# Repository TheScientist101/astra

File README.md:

<h1 align="center">astra</h1>

<h3 align="center">An open source, low cost, extensible brushed drone.</h3>

## What is Astra?

Astra is an `~80mm` brushed quadcopter. It it powered off of a single 1s Li-Po (`4.2V`), and uses four brushed motors.

Astra supports an optional FPV module, and includes a HAT-style pin interface on the flight controller.

We've also designed our own transmitter for Astra. The flight controller and transmitter use an `nRF24` to communicate with low latency.

Every part of Astra was designed from scratch - the flight controller, the transmitter, and the frame.

## Why is Astra?

Siddhant and I both love making things, but we've never made anything that moves before. What cooler of a thing is there that moves than a drone? With air voyage in our control, it would open the gate to even cooler projects, like imagine if you could play laser tag with a drone as your teammate or if you could have a drone that follows you around and takes pictures of you. The possibilities are endless!

That's why we decided to make our drone extensible. To me, modularity is the coolest part of any gadget. It allows you to add new features and capabilities without having to redesign the entire thing. Astra has a HAT-style pin interface called the DUCKDUCKGOOSE (Digital Unified Centralized Kibibit Device Universal Coding Knowledge Generic Operable Objective Service Extensible) Connector on the flight controller, which allows you to add new peripherals and sensors easily.

On the other hand, most drone projects we've seen online are expensive. While Hack Club is dope enough to have a [program that gives us free hardware](https://highway.hackclub.com), it is difficult to find a "DIY" drone that is relatively cheap that flies well. Since we wanted to make sure that our drone was actually good at flying, we decided to remove the onboard camera that we had in our initial design in place of a more traditional FPV system rather than just trying to make our own.

## Cost

All of the components for the drone and can be bought for around `$75`. (See the [`BOM`](./BOM.md) for more details!)

The bulk of this is actually the cost to buy the PCBs and stencil (which is anticipated to be around `$25`). The actual component cost is closer to `$50`.

> Note:
> Adding an FPV system to the drone is relatively costly. The FPV Camera + VTX module costs `$25`, which is actually on the cheaper end for these systems. The total cost with the FPV module is slightly less than `$100` before taxes and other fees.

(for hackclub) Even though the total cost of this drone is under `$150`, we will likely need to have multiple iterations of the PCB before we can get it working right.

## Technical Details

The Flight Controller uses an `STM32H750`. This is a powerful chip with plenty of GPIO pins for peripherals. We plan to implement a software OSD within the H7 for the FPV interface.

PCB files can be found within the `drone/pcb/` folder.

The Flight Controller uses the [betaflight](https://betaflight.com/) firmware. A betaflight config file as well as flashing instructions can be found in the `drone/firmware/` folder

The frame for the FC was designed in Onshape. CAD files can be found in `drone/cad/`;

**Peripherals**:

- `BMI270` - IMU
- `BMP388` - Barometer
- 2 `WS2812B`s
- 2 configurable buttons
- microSD Card Socket
- A 22 pin header for HAT-style extensions. Includes SWD, UART, SPI, I2C, and extra GPIOs.
- An extra UART connector.

The Ground Transmitter uses an `ESP32-C3-SuperMini` (a C3 chip similar to the XIAO that we already have on hand). It features:

- 3 `WS2812B`s
- 2 Joysticks, configured for mode 2 control
- 4 configurable buttons (+2 from the joysticks)

The PCB, firmware, and case for the transmitter can be found in the `controller/` folder

## Pictures

[**Full Schematic PDF**](assets/schematic.pdf)

**Copper Layers:**

**PCB 3D Render:**

**Controller PCB Render:**

**Controller Assembled Render:**

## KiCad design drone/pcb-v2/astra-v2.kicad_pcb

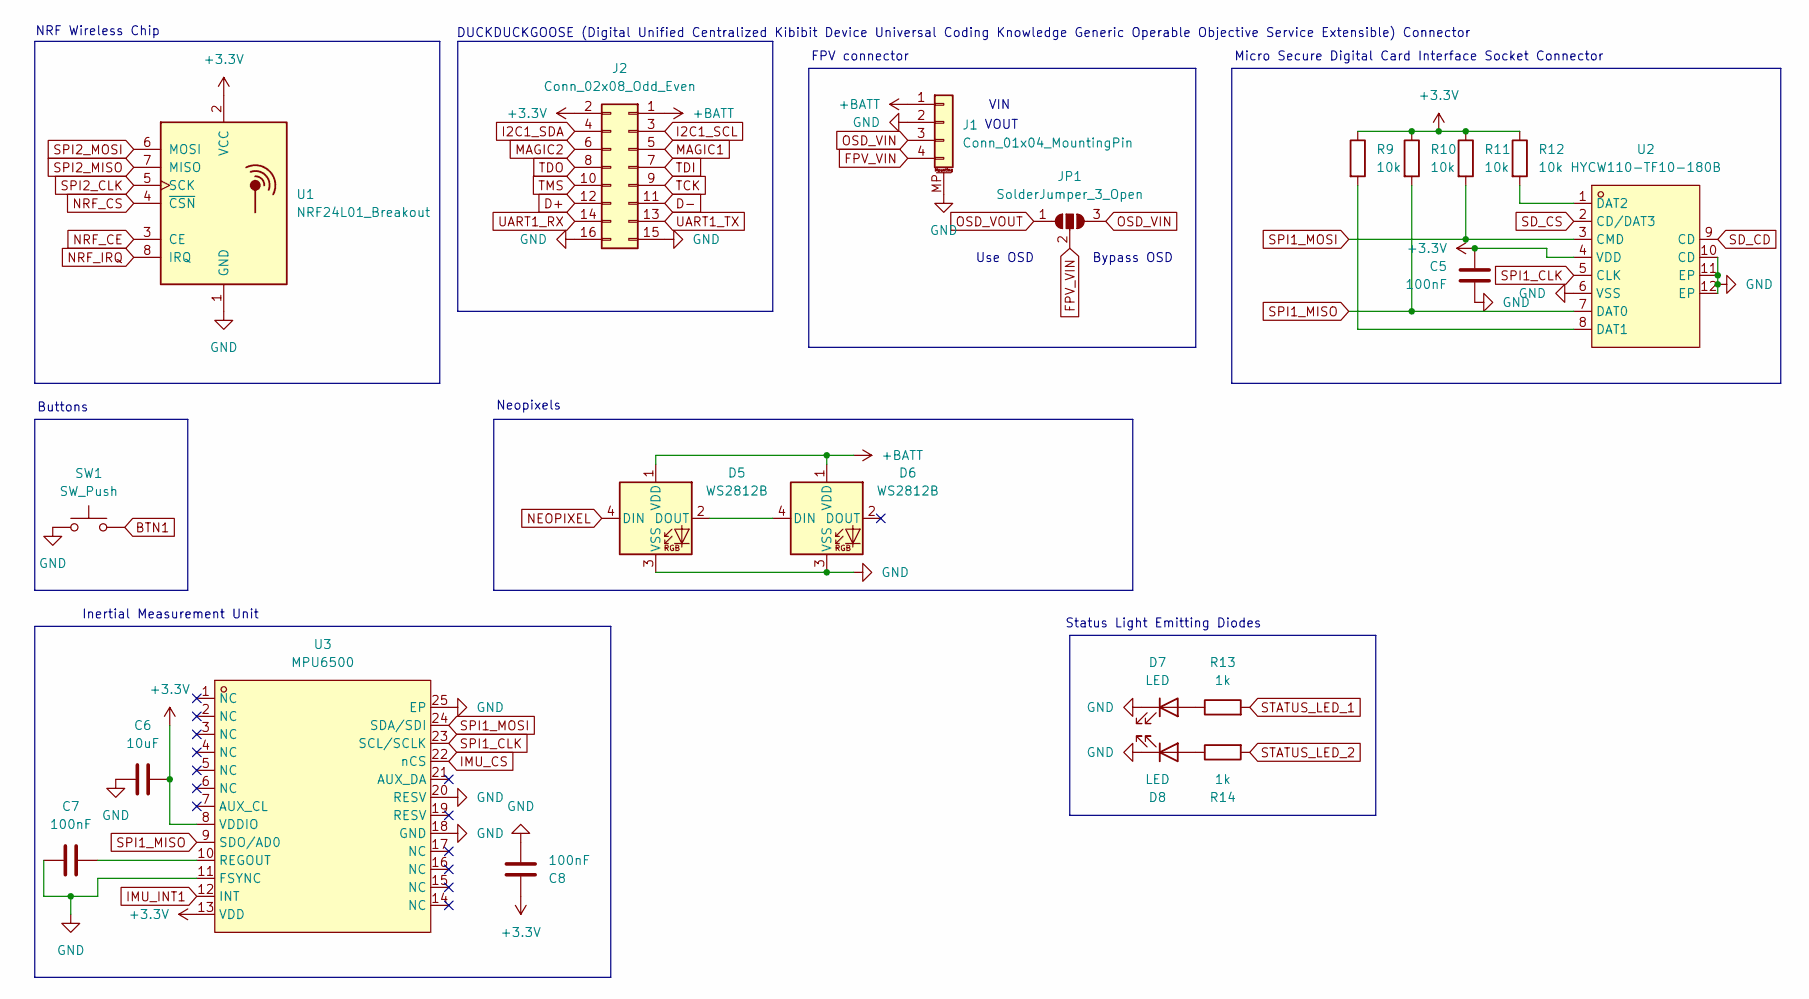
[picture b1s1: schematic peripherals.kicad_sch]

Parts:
C5: 100nF; C_0805_2012Metric_Pad1.18x1.45mm_HandSolder
C6: 10uF; C_0603_1608Metric
C7, C8: 100nF; C_0603_1608Metric; LCSC C14663
D5, D6: WS2812B; LED_WS2812B_PLCC4_5.0x5.0mm_P3.2mm
D7, D8: LED; LED_0805_2012Metric
J1: Conn_01x04_MountingPin; JST_SH_BM04B-SRSS-TB_1x04-1MP_P1.00mm_Vertical
J2: Conn_02x08_Odd_Even; PinHeader_2x08_P2.54mm_Vertical
JP1: SolderJumper_3_Open; SolderJumper-3_P1.3mm_Open_RoundedPad1.0x1.5mm
R9, R10, R11, R12: 10k; R_0805_2012Metric; LCSC C17414
R13, R14: 1k; R_0805_2012Metric_Pad1.20x1.40mm_HandSolder
SW1: SW_Push; SW-SMD_L4.0-W2.9-LS5.0
U1: NRF24L01_Breakout; nRF24L01_SMD_Breakout
U2: HYCW110-TF10-180B; SIM-SMD_HYCW110-TF10-180B; LCSC Part C2962030
U3: MPU6500; QFN-24-1EP_3x3mm_P0.4mm_EP1.75x1.6mm; LCSC C50278

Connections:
+3.3V: C5.1, C6.2, C8.1, J2.2, R9.1, R10.1, R11.1, R12.1, U1.2 (VCC), U2.4 (VDD), U3.8 (VDDIO), U3.13 (VDD); also elsewhere on the board
+BATT: D5.1 (VDD), D6.1 (VDD), J1.1, J2.1; also elsewhere on the board
BTN1: SW1.2; also elsewhere on the board
D+: J2.12; also elsewhere on the board
D-: J2.11; also elsewhere on the board
FPV_VIN: J1.4, JP1.2 (C)
GND: C5.2, C6.1, C7.2, C8.2, D5.3 (VSS), D6.3 (VSS), D7.1 (K), D8.1 (K), J1.2, J1.MP (MountPin), J2.15, J2.16, SW1.1, U1.1 (GND), U2.6 (VSS), U2.10 (CD), U2.11 (EP), U2.12 (EP), U3.11 (FSYNC), U3.18 (GND), U3.20 (RESV), U3.25 (EP); also elsewhere on the board
I2C1_SCL: J2.3; also elsewhere on the board
I2C1_SDA: J2.4; also elsewhere on the board
IMU_CS: U3.22 (nCS); also elsewhere on the board
IMU_INT1: U3.12 (INT); also elsewhere on the board
MAGIC1: J2.5; also elsewhere on the board
MAGIC2: J2.6; also elsewhere on the board
NEOPIXEL: D5.4 (DIN); also elsewhere on the board
NRF_CE: U1.3 (CE); also elsewhere on the board
NRF_CS: U1.4 (~CSN); also elsewhere on the board
NRF_IRQ: U1.8 (IRQ); also elsewhere on the board
unnamed: D5.2 (DOUT), D6.4 (DIN)
unnamed: D7.2 (A), R13.1
unnamed: D8.2 (A), R14.1
unnamed: R9.2, U2.8 (DAT1)
unnamed: R12.2, U2.1 (DAT2)
unnamed: C7.1, U3.10 (REGOUT)
OSD_VIN: J1.3, JP1.3 (B)
OSD_VOUT: JP1.1 (A)
SD_CD: U2.9 (CD); also elsewhere on the board
SD_CS: U2.2 (CD/DAT3); also elsewhere on the board
SPI1_CLK: U2.5 (CLK), U3.23 (SCL/SCLK); also elsewhere on the board
SPI1_MISO: R10.2, U2.7 (DAT0), U3.9 (SDO/AD0); also elsewhere on the board
SPI1_MOSI: R11.2, U2.3 (CMD), U3.24 (SDA/SDI); also elsewhere on the board
SPI2_CLK: U1.5 (SCK); also elsewhere on the board
SPI2_MISO: U1.7 (MISO); also elsewhere on the board
SPI2_MOSI: U1.6 (MOSI); also elsewhere on the board
STATUS_LED_1: R13.2; also elsewhere on the board
STATUS_LED_2: R14.2; also elsewhere on the board
TCK: J2.9; also elsewhere on the board
TDI: J2.7; also elsewhere on the board
TDO: J2.8; also elsewhere on the board
TMS: J2.10; also elsewhere on the board
UART1_RX: J2.14; also elsewhere on the board
UART1_TX: J2.13; also elsewhere on the board

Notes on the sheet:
Buttons
FPV connector
Neopixels
DUCKDUCKGOOSE (Digital Unified Centralized Kibibit Device Universal Coding Knowledge Generic Operable Objective Service Extensible) Connector
Use OSD
NRF Wireless Chip
Status Light Emitting Diodes
VOUT
Bypass OSD
Micro Secure Digital Card Interface Socket Connector
Inertial Measurement Unit
VIN

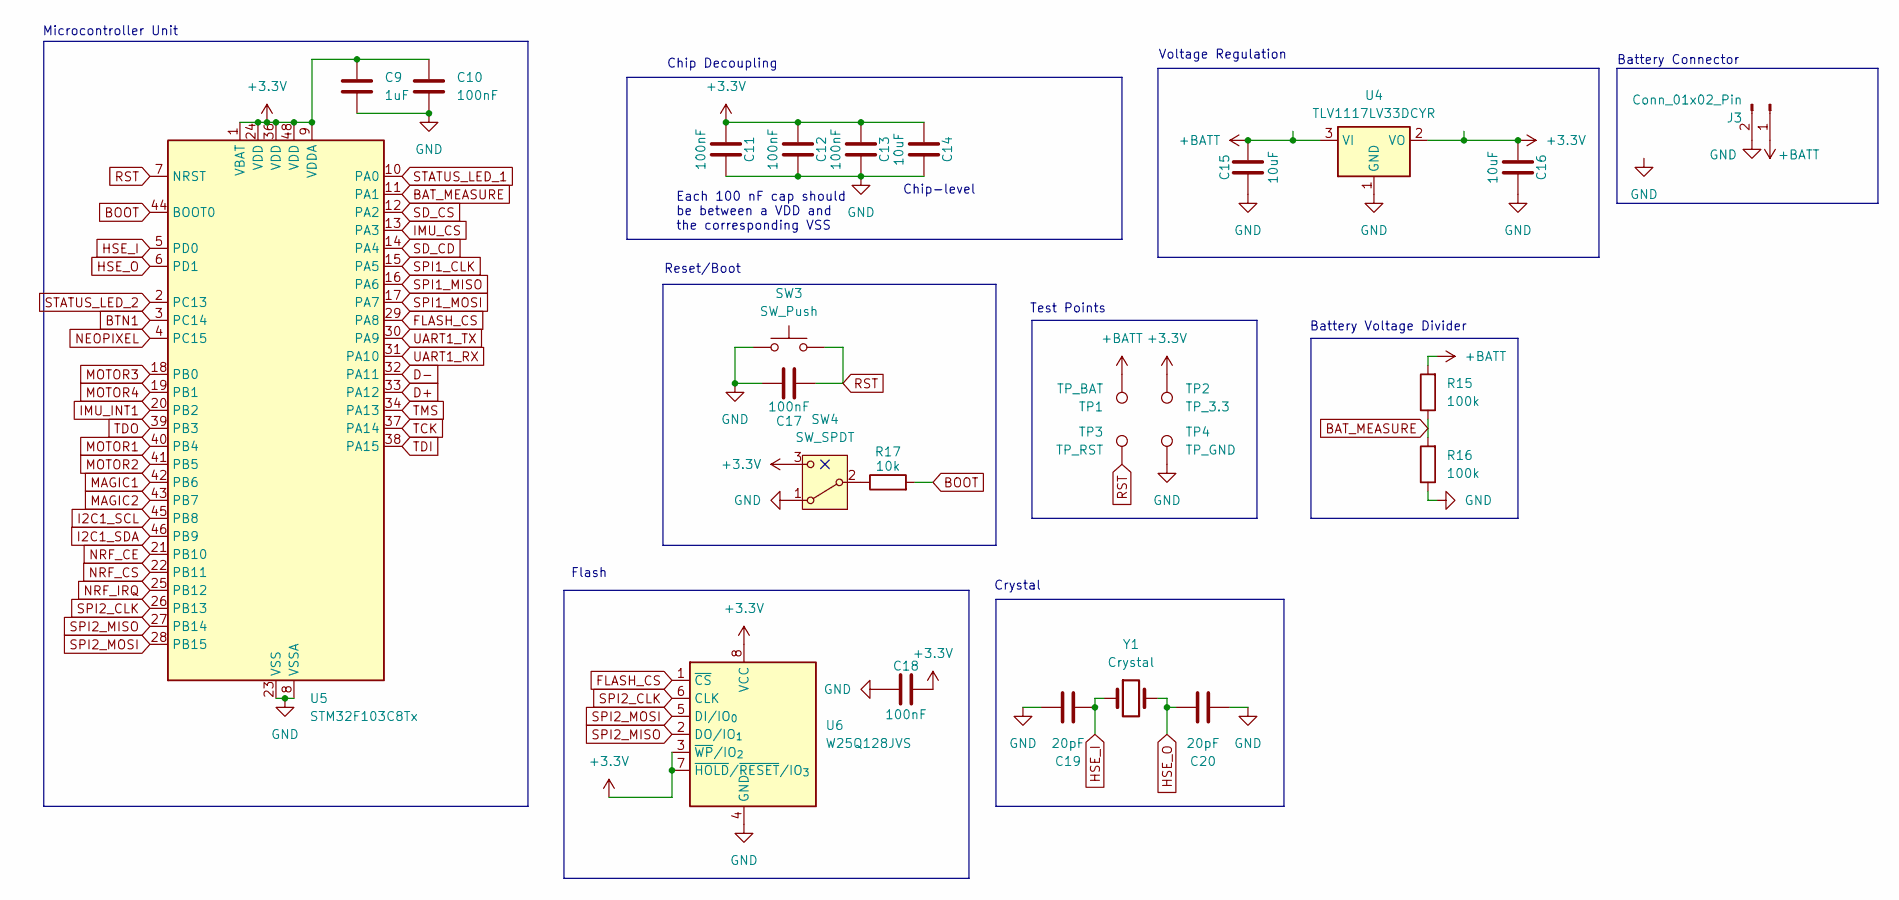
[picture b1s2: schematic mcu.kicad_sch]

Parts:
C9: 1uF; C_0603_1608Metric; LCSC C15849
C10, C11, C12, C13, C18: 100nF; C_0603_1608Metric; LCSC C14663
C14: 10uF; C_0603_1608Metric; LCSC C19702
C15, C16: 10uF; C_0805_2012Metric_Pad1.18x1.45mm_HandSolder
C17: 100nF; C_0805_2012Metric_Pad1.18x1.45mm_HandSolder
C19, C20: 20pF; C_0603_1608Metric; LCSC C1648
J3: Conn_01x02_Pin; SolderWire-0.1sqmm_1x02_P3.6mm_D0.4mm_OD1mm
R15, R16: 100k; R_0603_1608Metric; LCSC C25803
R17: 10k; R_0805_2012Metric; LCSC C17414
SW3: SW_Push; SW-SMD_L4.0-W2.9-LS5.0
SW4: SW_SPDT; SW_Slide-03_Wuerth-WS-SLTV_10x2.5x6.4_P2.54mm
TP1: TP_BAT; TestPoint_Pad_D2.0mm
TP2: TP_3.3; TestPoint_Pad_D2.0mm
TP3: TP_RST; TestPoint_Pad_D2.0mm
TP4: TP_GND; TestPoint_Pad_D2.0mm
U4: TLV1117LV33DCYR; SOT-223-3_TabPin2
U5: STM32F103C8Tx; LQFP-48_7x7mm_P0.5mm; LCSC C8734
U6: W25Q128JVS; SOIC-8_5.3x5.3mm_P1.27mm; LCSC C97521
Y1: Crystal; Crystal_SMD_5032-2Pin_5.0x3.2mm; LCSC C115962

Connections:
+3.3V: C9.1, C10.1, C11.1, C12.1, C13.1, C14.1, C16.1, C18.2, SW4.3 (C), TP2.1, U4.2 (VO), U5.1 (VBAT), U5.9 (VDDA), U5.24 (VDD), U5.36 (VDD), U5.48 (VDD), U6.3 (~WP/IO_{2}), U6.7 (~HOLD/~RESET/IO_{3}), U6.8 (VCC); also elsewhere on the board
+BATT: C15.2, J3.1, R15.2, TP1.1, U4.3 (VI); also elsewhere on the board
BAT_MEASURE: R15.1, R16.2, U5.11 (PA1)
BOOT: R17.2, U5.44 (BOOT0)
BTN1: U5.3 (PC14); also elsewhere on the board
D+: U5.33 (PA12); also elsewhere on the board
D-: U5.32 (PA11); also elsewhere on the board
FLASH_CS: U5.29 (PA8), U6.1 (~CS)
GND: C9.2, C10.2, C11.2, C12.2, C13.2, C14.2, C15.1, C16.2, C17.2, C18.1, C19.1, C20.2, J3.2, R16.1, SW3.1, SW4.1 (A), TP4.1, U4.1 (GND), U5.8 (VSSA), U5.23 (VSS), U5.35 (VSS), U5.47 (VSS), U6.4 (GND); also elsewhere on the board
HSE_I: C19.2, U5.5 (PD0), Y1.1
HSE_O: C20.1, U5.6 (PD1), Y1.2
I2C1_SCL: U5.45 (PB8); also elsewhere on the board
I2C1_SDA: U5.46 (PB9); also elsewhere on the board
IMU_CS: U5.13 (PA3); also elsewhere on the board
IMU_INT1: U5.20 (PB2); also elsewhere on the board
MAGIC1: U5.42 (PB6); also elsewhere on the board
MAGIC2: U5.43 (PB7); also elsewhere on the board
MOTOR1: U5.40 (PB4); also elsewhere on the board
MOTOR2: U5.41 (PB5); also elsewhere on the board
MOTOR3: U5.18 (PB0); also elsewhere on the board
MOTOR4: U5.19 (PB1); also elsewhere on the board
NEOPIXEL: U5.4 (PC15); also elsewhere on the board
NRF_CE: U5.21 (PB10); also elsewhere on the board
NRF_CS: U5.22 (PB11); also elsewhere on the board
NRF_IRQ: U5.25 (PB12); also elsewhere on the board
unnamed: R17.1, SW4.2 (B)
RST: C17.1, SW3.2, TP3.1, U5.7 (NRST)
SD_CD: U5.14 (PA4); also elsewhere on the board
SD_CS: U5.12 (PA2); also elsewhere on the board
SPI1_CLK: U5.15 (PA5); also elsewhere on the board
SPI1_MISO: U5.16 (PA6); also elsewhere on the board
SPI1_MOSI: U5.17 (PA7); also elsewhere on the board
SPI2_CLK: U5.26 (PB13), U6.6 (CLK); also elsewhere on the board
SPI2_MISO: U5.27 (PB14), U6.2 (DO/IO_{1}); also elsewhere on the board
SPI2_MOSI: U5.28 (PB15), U6.5 (DI/IO_{0}); also elsewhere on the board
STATUS_LED_1: U5.10 (PA0); also elsewhere on the board
STATUS_LED_2: U5.2 (PC13); also elsewhere on the board
TCK: U5.37 (PA14); also elsewhere on the board
TDI: U5.38 (PA15); also elsewhere on the board
TDO: U5.39 (PB3); also elsewhere on the board
TMS: U5.34 (PA13); also elsewhere on the board
UART1_RX: U5.31 (PA10); also elsewhere on the board
UART1_TX: U5.30 (PA9); also elsewhere on the board

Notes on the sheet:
Microcontroller Unit
Flash
Each 100 nF cap should be between a VDD and the corresponding VSS
Battery Voltage Divider
Chip Decoupling
Crystal
Test Points
Chip-level
Battery Connector
Reset/Boot
Voltage Regulation

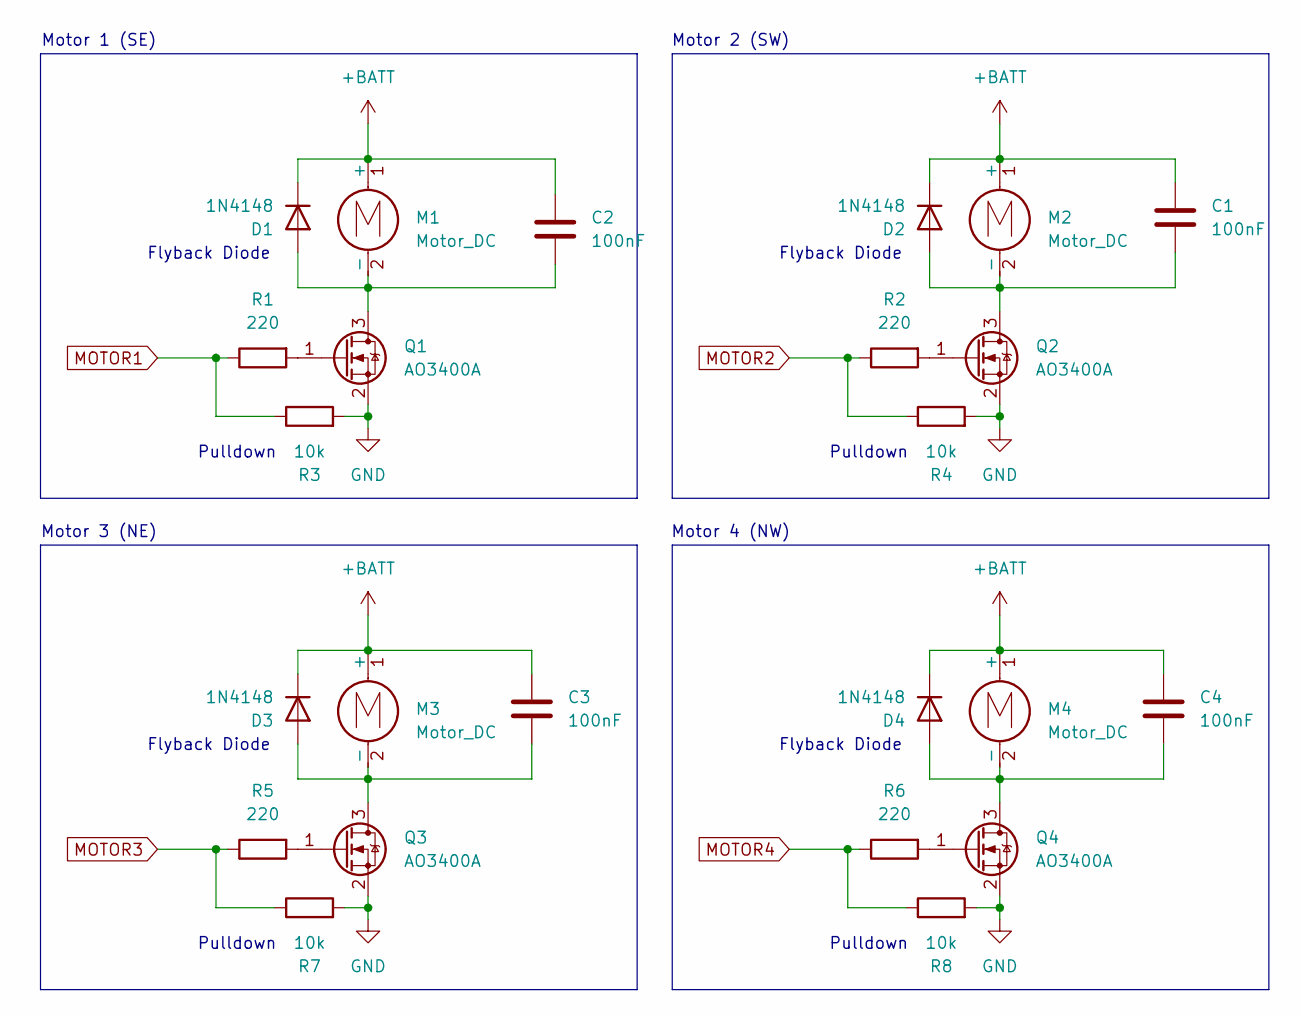
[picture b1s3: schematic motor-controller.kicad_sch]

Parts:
C1, C2, C3, C4: 100nF; C_0805_2012Metric_Pad1.18x1.45mm_HandSolder
D1, D2, D3, D4: 1N4148; D_SOD-323; LCSC C2128
M1, M2, M3, M4: Motor_DC; SolderWire-0.1sqmm_1x02_P3.6mm_D0.4mm_OD1mm
Q1, Q2, Q3, Q4: AO3400A; SOT-23-3; LCSC C20917
R1, R2, R5, R6: 220; R_0805_2012Metric; LCSC C17557
R3, R4, R7, R8: 10k; R_0805_2012Metric; LCSC C17414

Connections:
+BATT: C1.1, C2.1, C3.1, C4.1, D1.1 (K), D2.1 (K), D3.1 (K), D4.1 (K), M1.1 (+), M2.1 (+), M3.1 (+), M4.1 (+); also elsewhere on the board
GND: Q1.2 (S), Q2.2 (S), Q3.2 (S), Q4.2 (S), R3.2, R4.2, R7.2, R8.2; also elsewhere on the board
MOTOR1: R1.1, R3.1; also elsewhere on the board
MOTOR2: R2.1, R4.1; also elsewhere on the board
MOTOR3: R5.1, R7.1; also elsewhere on the board
MOTOR4: R6.1, R8.1; also elsewhere on the board
unnamed: C2.2, D1.2 (A), M1.2 (-), Q1.3 (D)
unnamed: C1.2, D2.2 (A), M2.2 (-), Q2.3 (D)
unnamed: C3.2, D3.2 (A), M3.2 (-), Q3.3 (D)
unnamed: C4.2, D4.2 (A), M4.2 (-), Q4.3 (D)
unnamed: Q1.1 (G), R1.2
unnamed: Q2.1 (G), R2.2
unnamed: Q3.1 (G), R5.2
unnamed: Q4.1 (G), R6.2

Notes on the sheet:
Pulldown
Motor 2 (SW)
Flyback Diode
Motor 1 (SE)
Motor 3 (NE)
Motor 4 (NW)

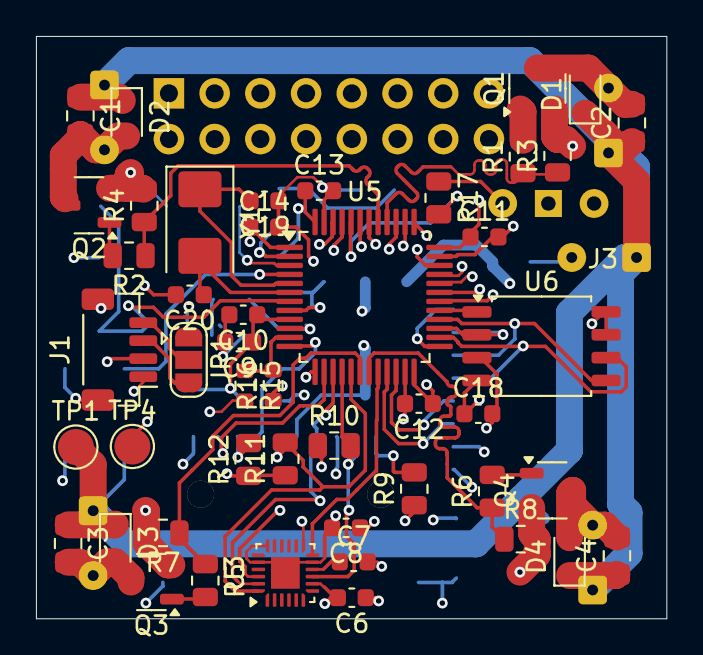
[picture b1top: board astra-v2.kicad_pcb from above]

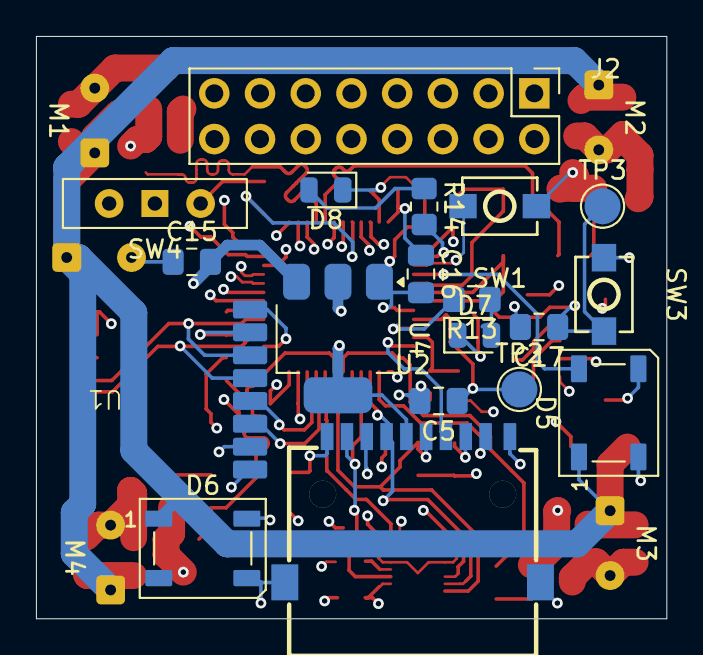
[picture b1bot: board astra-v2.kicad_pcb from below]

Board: 4 copper layers, 35.0 x 32.3 mm, 71 parts (23 on the bottom side), 59 nets.

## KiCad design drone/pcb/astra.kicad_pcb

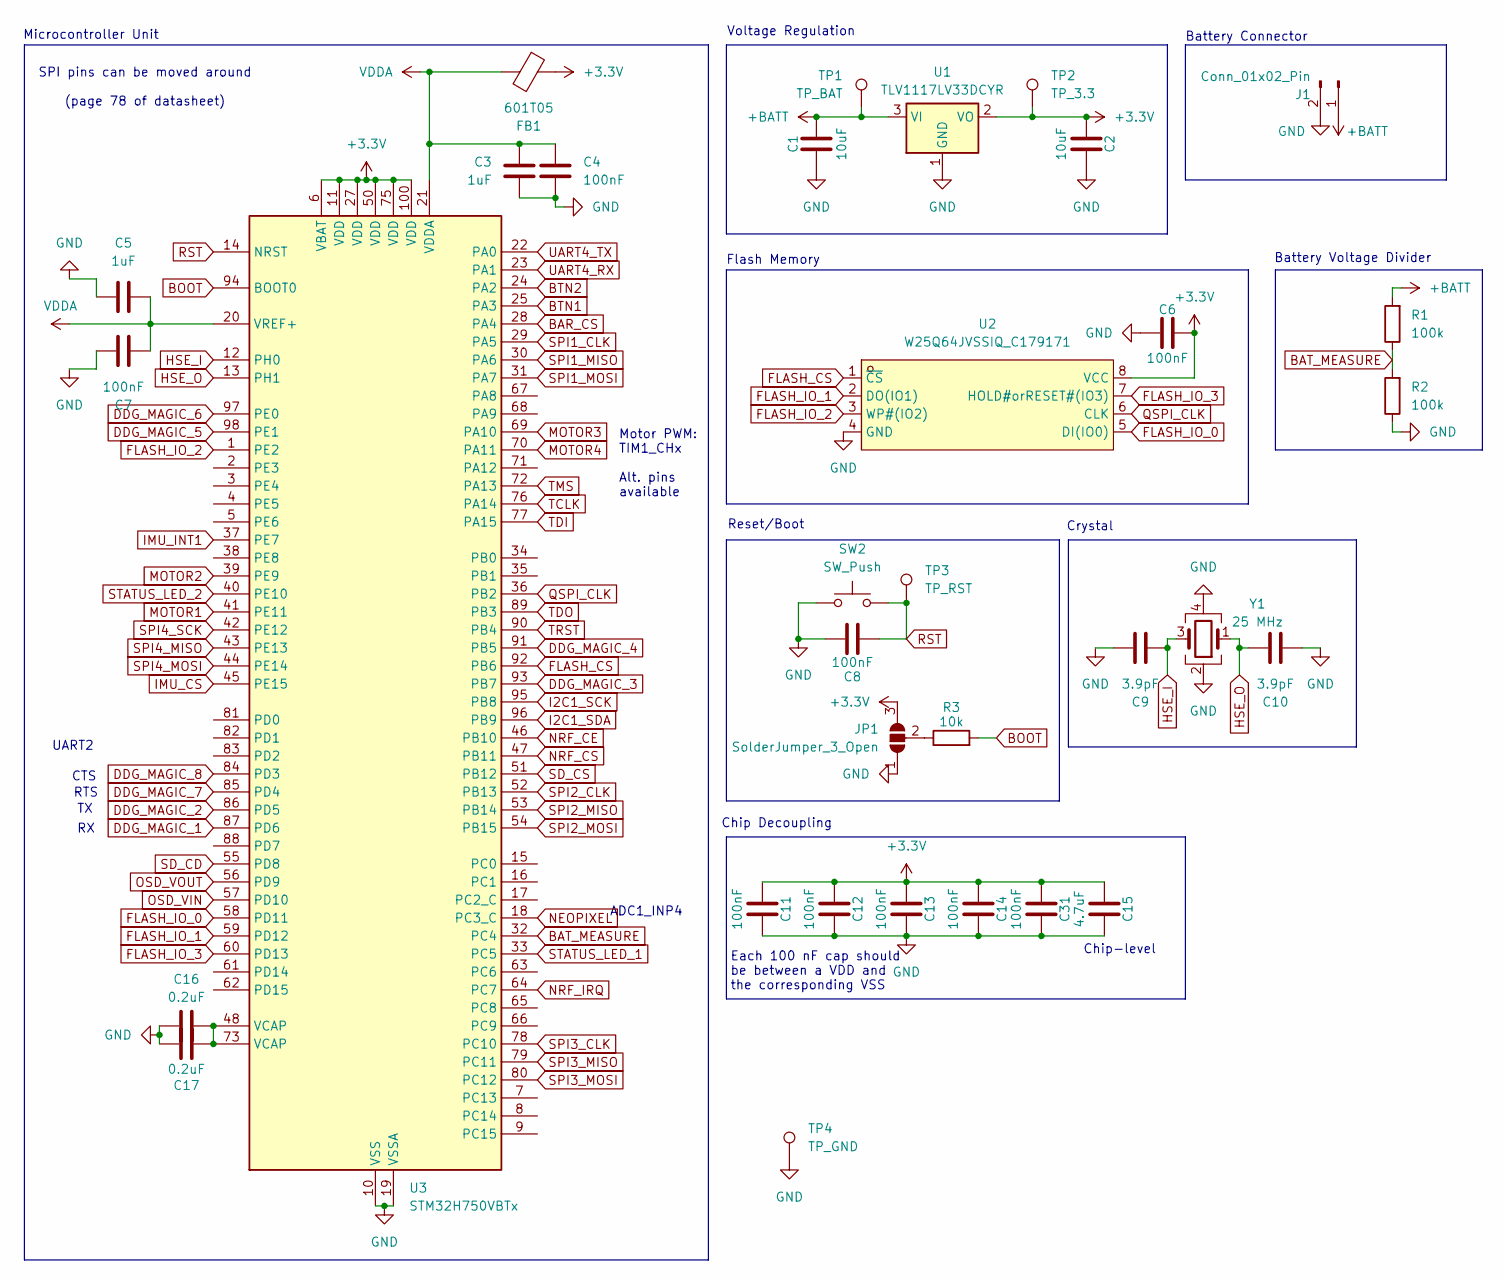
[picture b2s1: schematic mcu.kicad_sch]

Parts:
C1, C2: 10uF; C_0805_2012Metric_Pad1.18x1.45mm_HandSolder
C3, C5: 1uF; C_0805_2012Metric_Pad1.18x1.45mm_HandSolder
C4, C6, C7, C8, C11, C12, C13, C14, C31: 100nF; C_0805_2012Metric_Pad1.18x1.45mm_HandSolder
C9, C10: 3.9pF; C_0603_1608Metric_Pad1.08x0.95mm_HandSolder
C15: 4.7uF; C_0805_2012Metric_Pad1.18x1.45mm_HandSolder
C16, C17: 0.2uF; C_0805_2012Metric_Pad1.18x1.45mm_HandSolder
FB1: 601T05; L_0603_1608Metric_Pad1.05x0.95mm_HandSolder
J1: Conn_01x02_Pin; SolderWire-0.1sqmm_1x02_P3.6mm_D0.4mm_OD1mm
JP1: SolderJumper_3_Open; SolderJumper-3_P1.3mm_Open_RoundedPad1.0x1.5mm
R1, R2: 100k; R_0805_2012Metric_Pad1.20x1.40mm_HandSolder
R3: 10k; R_0805_2012Metric_Pad1.20x1.40mm_HandSolder
SW2: SW_Push; SW-SMD_L4.0-W2.9-LS5.0
TP1: TP_BAT; TestPoint_Pad_D2.0mm
TP2: TP_3.3; TestPoint_Pad_D2.0mm
TP3: TP_RST; TestPoint_Pad_D2.0mm
TP4: TP_GND; TestPoint_Pad_D2.0mm
U1: TLV1117LV33DCYR; SOT-223-3_TabPin2
U2: W25Q64JVSSIQ_C179171; SOIC-8_5.3x5.3mm_P1.27mm; LCSC Part C179171
U3: STM32H750VBTx; LQFP-100_14x14mm_P0.5mm
Y1: 25 MHz; Crystal_SMD_3225-4Pin_3.2x2.5mm_HandSoldering

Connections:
+3.3V: C2.1, C6.2, C11.1, C12.1, C13.1, C14.1, C15.1, C31.1, FB1.1, JP1.3 (B), TP2.1, U1.2 (VO), U2.8 (VCC), U3.6 (VBAT), U3.11 (VDD), U3.27 (VDD), U3.50 (VDD), U3.75 (VDD), U3.100 (VDD); also elsewhere on the board
+BATT: C1.2, J1.1, R1.2, TP1.1, U1.3 (VI); also elsewhere on the board
BAR_CS: U3.28 (PA4); also elsewhere on the board
BAT_MEASURE: R1.1, R2.2, U3.32 (PC4)
BOOT: R3.2, U3.94 (BOOT0)
BTN1: U3.25 (PA3); also elsewhere on the board
BTN2: U3.24 (PA2); also elsewhere on the board
DDG_MAGIC_1: U3.87 (PD6); also elsewhere on the board
DDG_MAGIC_2: U3.86 (PD5); also elsewhere on the board
DDG_MAGIC_3: U3.93 (PB7); also elsewhere on the board
DDG_MAGIC_4: U3.91 (PB5); also elsewhere on the board
DDG_MAGIC_5: U3.98 (PE1); also elsewhere on the board
DDG_MAGIC_6: U3.97 (PE0); also elsewhere on the board
DDG_MAGIC_7: U3.85 (PD4); also elsewhere on the board
DDG_MAGIC_8: U3.84 (PD3); also elsewhere on the board
FLASH_CS: U2.1 (~CS), U3.92 (PB6)
FLASH_IO_0: U2.5 (DI(IO0)), U3.58 (PD11)
FLASH_IO_1: U2.2 (DO(IO1)), U3.59 (PD12)
FLASH_IO_2: U2.3 (WP#(IO2)), U3.1 (PE2)
FLASH_IO_3: U2.7 (HOLD#orRESET#(IO3)), U3.60 (PD13)
GND: C1.1, C2.2, C3.2, C4.2, C5.1, C6.1, C7.1, C8.2, C9.1, C10.2, C11.2, C12.2, C13.2, C14.2, C15.2, C16.1, C17.1, C31.2, J1.2, JP1.1 (A), R2.1, SW2.1, TP4.1, U1.1 (GND), U2.4 (GND), U3.10 (VSS), U3.19 (VSSA), U3.26 (VSS), U3.49 (VSS), U3.74 (VSS), U3.99 (VSS), Y1.2, Y1.4; also elsewhere on the board
HSE_I: C9.2, U3.12 (PH0), Y1.3
HSE_O: C10.1, U3.13 (PH1), Y1.1
I2C1_SCK: U3.95 (PB8); also elsewhere on the board
I2C1_SDA: U3.96 (PB9); also elsewhere on the board
IMU_CS: U3.45 (PE15); also elsewhere on the board
IMU_INT1: U3.37 (PE7); also elsewhere on the board
MOTOR1: U3.41 (PE11); also elsewhere on the board
MOTOR2: U3.39 (PE9); also elsewhere on the board
MOTOR3: U3.69 (PA10); also elsewhere on the board
MOTOR4: U3.70 (PA11); also elsewhere on the board
NEOPIXEL: U3.18 (PC3_C); also elsewhere on the board
NRF_CE: U3.46 (PB10); also elsewhere on the board
NRF_CS: U3.47 (PB11); also elsewhere on the board
NRF_IRQ: U3.64 (PC7); also elsewhere on the board
unnamed: C16.2, C17.2, U3.48 (VCAP), U3.73 (VCAP)
unnamed: JP1.2 (C), R3.1
OSD_VIN: U3.57 (PD10); also elsewhere on the board
OSD_VOUT: U3.56 (PD9); also elsewhere on the board
QSPI_CLK: U2.6 (CLK), U3.36 (PB2)
RST: C8.1, SW2.2, TP3.1, U3.14 (NRST); also elsewhere on the board
SD_CD: U3.55 (PD8); also elsewhere on the board
SD_CS: U3.51 (PB12); also elsewhere on the board
SPI1_CLK: U3.29 (PA5); also elsewhere on the board
SPI1_MISO: U3.30 (PA6); also elsewhere on the board
SPI1_MOSI: U3.31 (PA7); also elsewhere on the board
SPI2_CLK: U3.52 (PB13); also elsewhere on the board
SPI2_MISO: U3.53 (PB14); also elsewhere on the board
SPI2_MOSI: U3.54 (PB15); also elsewhere on the board
SPI3_CLK: U3.78 (PC10); also elsewhere on the board
SPI3_MISO: U3.79 (PC11); also elsewhere on the board
SPI3_MOSI: U3.80 (PC12); also elsewhere on the board
SPI4_MISO: U3.43 (PE13); also elsewhere on the board
SPI4_MOSI: U3.44 (PE14); also elsewhere on the board
SPI4_SCK: U3.42 (PE12); also elsewhere on the board
STATUS_LED_1: U3.33 (PC5); also elsewhere on the board
STATUS_LED_2: U3.40 (PE10); also elsewhere on the board
TCLK: U3.76 (PA14); also elsewhere on the board
TDI: U3.77 (PA15); also elsewhere on the board
TDO: U3.89 (PB3); also elsewhere on the board
TMS: U3.72 (PA13); also elsewhere on the board
TRST: U3.90 (PB4); also elsewhere on the board
UART4_RX: U3.23 (PA1); also elsewhere on the board
UART4_TX: U3.22 (PA0); also elsewhere on the board
VDDA: C3.1, C4.1, C5.2, C7.2, FB1.2, U3.20 (VREF+), U3.21 (VDDA)

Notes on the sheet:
Reset/Boot
Crystal
Voltage Regulation
UART2
CTS
Chip-level
Battery Connector
Flash Memory
Battery Voltage Divider
Microcontroller Unit
Each 100 nF cap should be between a VDD and the corresponding VSS
SPI pins can be moved around (page 78 of datasheet)
ADC1_INP4
Motor PWM: TIM1_CHx Alt. pins available
RTS
Chip Decoupling

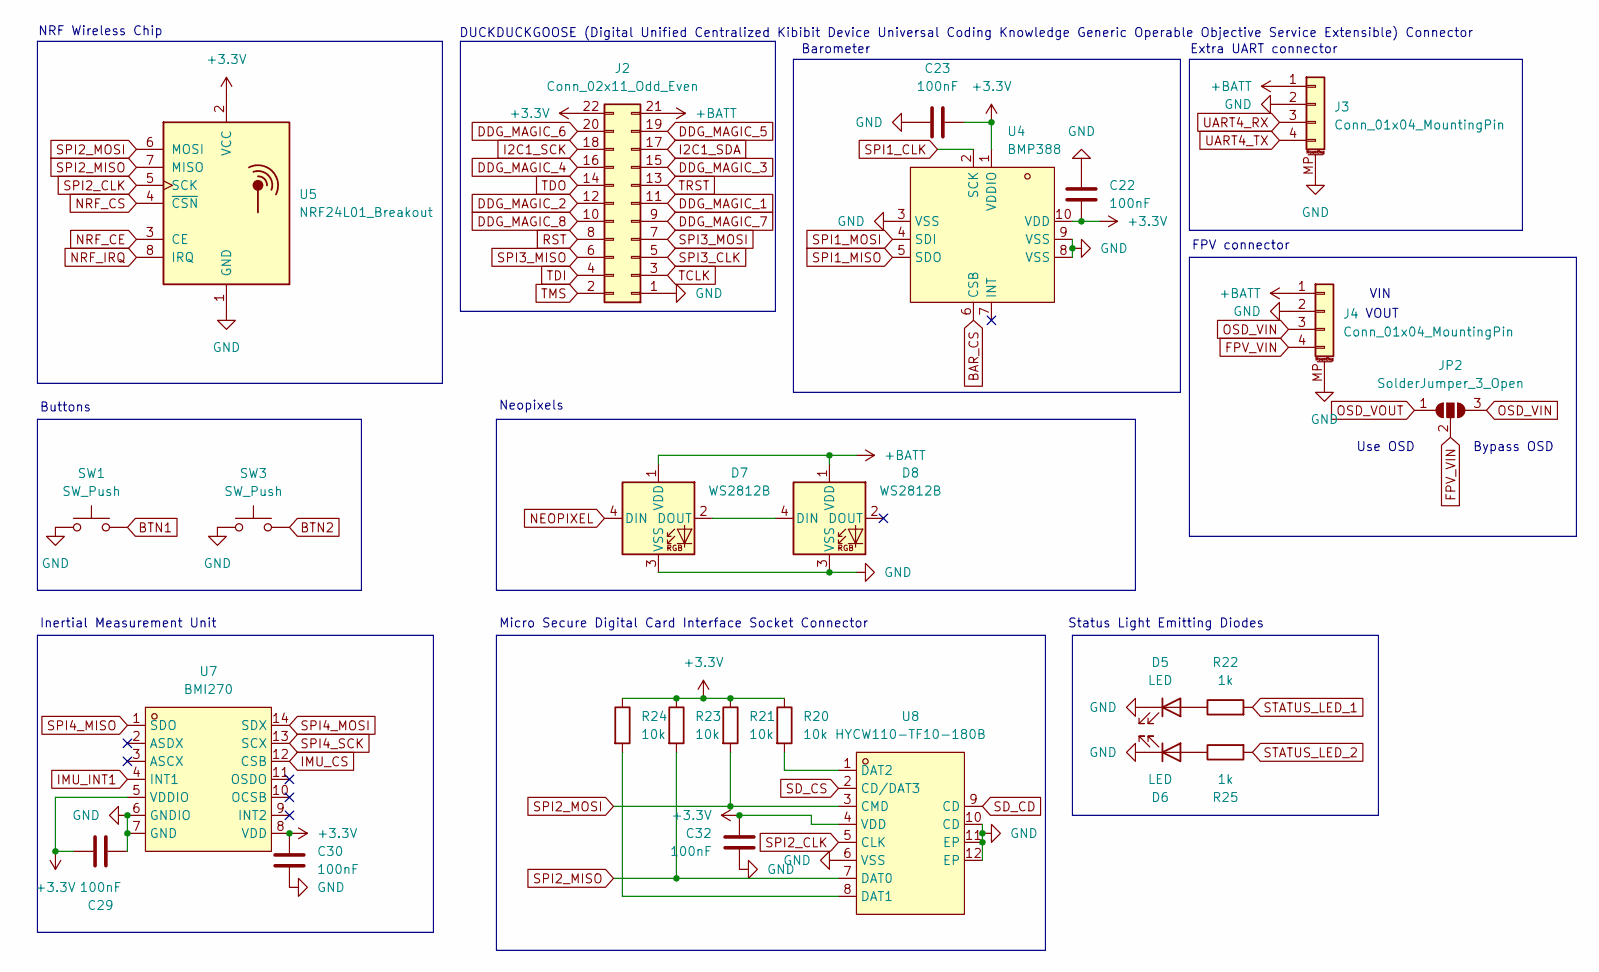
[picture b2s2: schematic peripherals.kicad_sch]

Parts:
C22, C23, C29, C30, C32: 100nF; C_0805_2012Metric_Pad1.18x1.45mm_HandSolder
D5, D6: LED; LED_0805_2012Metric
D7, D8: WS2812B; LED_WS2812B_PLCC4_5.0x5.0mm_P3.2mm
J2: Conn_02x11_Odd_Even; PinHeader_2x11_P2.54mm_Vertical
J3, J4: Conn_01x04_MountingPin; JST_SH_BM04B-SRSS-TB_1x04-1MP_P1.00mm_Vertical
JP2: SolderJumper_3_Open; SolderJumper-3_P1.3mm_Open_RoundedPad1.0x1.5mm
R20, R21, R23, R24: 10k; R_0805_2012Metric_Pad1.20x1.40mm_HandSolder
R22, R25: 1k; R_0805_2012Metric
SW1, SW3: SW_Push; SW-SMD_L4.0-W2.9-LS5.0
U4: BMP388; ST_HLGA-10_2x2mm_P0.5mm_LayoutBorder3x2y; LCSC Part C779278
U5: NRF24L01_Breakout; nRF24L01_SMD_Breakout
U7: BMI270; Bosch_LGA-14_3x2.5mm_P0.5mm; LCSC Part C2836813
U8: HYCW110-TF10-180B; SIM-SMD_HYCW110-TF10-180B; LCSC Part C2962030

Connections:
+3.3V: C22.2, C23.2, C29.1, C30.1, C32.1, J2.22, R20.1, R21.1, R23.1, R24.1, U4.1 (VDDIO), U4.10 (VDD), U5.2 (VCC), U7.5 (VDDIO), U7.8 (VDD), U8.4 (VDD); also elsewhere on the board
+BATT: D7.1 (VDD), D8.1 (VDD), J2.21, J3.1, J4.1; also elsewhere on the board
BAR_CS: U4.6 (CSB); also elsewhere on the board
BTN1: SW1.2; also elsewhere on the board
BTN2: SW3.2; also elsewhere on the board
DDG_MAGIC_1: J2.11; also elsewhere on the board
DDG_MAGIC_2: J2.12; also elsewhere on the board
DDG_MAGIC_3: J2.15; also elsewhere on the board
DDG_MAGIC_4: J2.16; also elsewhere on the board
DDG_MAGIC_5: J2.19; also elsewhere on the board
DDG_MAGIC_6: J2.20; also elsewhere on the board
DDG_MAGIC_7: J2.9; also elsewhere on the board
DDG_MAGIC_8: J2.10; also elsewhere on the board
FPV_VIN: J4.4, JP2.2 (C)
GND: C22.1, C23.1, C29.2, C30.2, C32.2, D5.1 (K), D6.1 (K), D7.3 (VSS), D8.3 (VSS), J2.1, J3.2, J3.MP (MountPin), J4.2, J4.MP (MountPin), SW1.1, SW3.1, U4.3 (VSS), U4.8 (VSS), U4.9 (VSS), U5.1 (GND), U7.6 (GNDIO), U7.7 (GND), U8.6 (VSS), U8.10 (CD), U8.11 (EP), U8.12 (EP); also elsewhere on the board
I2C1_SCK: J2.18; also elsewhere on the board
I2C1_SDA: J2.17; also elsewhere on the board
IMU_CS: U7.12 (CSB); also elsewhere on the board
IMU_INT1: U7.4 (INT1); also elsewhere on the board
NEOPIXEL: D7.4 (DIN); also elsewhere on the board
NRF_CE: U5.3 (CE); also elsewhere on the board
NRF_CS: U5.4 (~CSN); also elsewhere on the board
NRF_IRQ: U5.8 (IRQ); also elsewhere on the board
unnamed: D5.2 (A), R22.1
unnamed: D6.2 (A), R25.1
unnamed: D7.2 (DOUT), D8.4 (DIN)
unnamed: R24.2, U8.8 (DAT1)
unnamed: R20.2, U8.1 (DAT2)
OSD_VIN: J4.3, JP2.3 (B); also elsewhere on the board
OSD_VOUT: JP2.1 (A); also elsewhere on the board
RST: J2.8; also elsewhere on the board
SD_CD: U8.9 (CD); also elsewhere on the board
SD_CS: U8.2 (CD/DAT3); also elsewhere on the board
SPI1_CLK: U4.2 (SCK); also elsewhere on the board
SPI1_MISO: U4.5 (SDO); also elsewhere on the board
SPI1_MOSI: U4.4 (SDI); also elsewhere on the board
SPI2_CLK: U5.5 (SCK), U8.5 (CLK); also elsewhere on the board
SPI2_MISO: R23.2, U5.7 (MISO), U8.7 (DAT0); also elsewhere on the board
SPI2_MOSI: R21.2, U5.6 (MOSI), U8.3 (CMD); also elsewhere on the board
SPI3_CLK: J2.5; also elsewhere on the board
SPI3_MISO: J2.6; also elsewhere on the board
SPI3_MOSI: J2.7; also elsewhere on the board
SPI4_MISO: U7.1 (SDO); also elsewhere on the board
SPI4_MOSI: U7.14 (SDX); also elsewhere on the board
SPI4_SCK: U7.13 (SCX); also elsewhere on the board
STATUS_LED_1: R22.2; also elsewhere on the board
STATUS_LED_2: R25.2; also elsewhere on the board
TCLK: J2.3; also elsewhere on the board
TDI: J2.4; also elsewhere on the board
TDO: J2.14; also elsewhere on the board
TMS: J2.2; also elsewhere on the board
TRST: J2.13; also elsewhere on the board
UART4_RX: J3.3; also elsewhere on the board
UART4_TX: J3.4; also elsewhere on the board

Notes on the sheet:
Buttons
FPV connector
Neopixels
Extra UART connector
DUCKDUCKGOOSE (Digital Unified Centralized Kibibit Device Universal Coding Knowledge Generic Operable Objective Service Extensible) Connector
Barometer
Use OSD
NRF Wireless Chip
Status Light Emitting Diodes
VOUT
Bypass OSD
Micro Secure Digital Card Interface Socket Connector
Inertial Measurement Unit
VIN

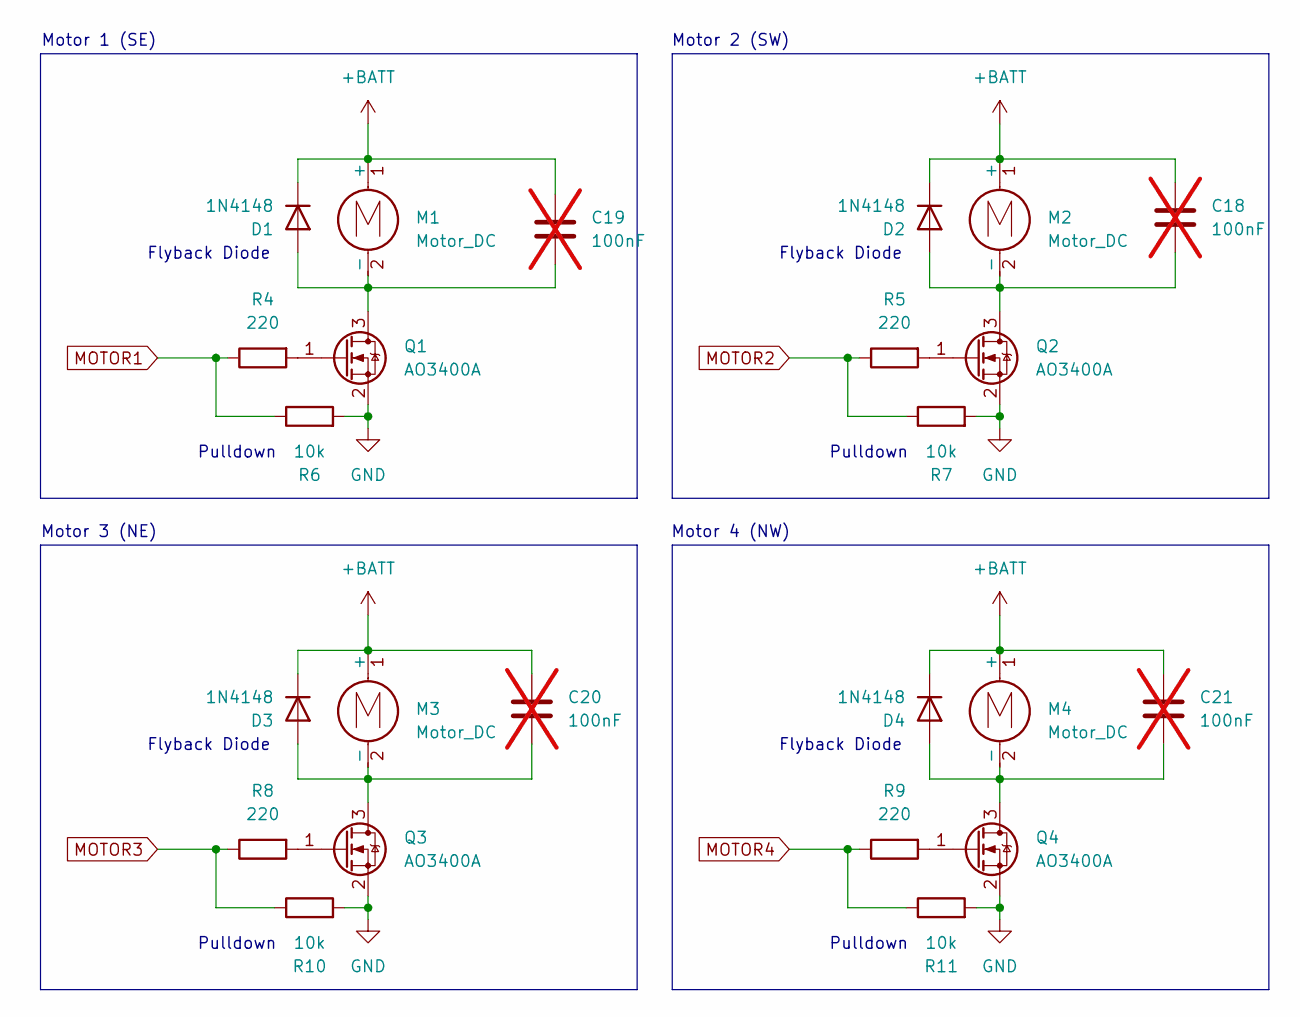
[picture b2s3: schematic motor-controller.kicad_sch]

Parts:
C18, C19, C20, C21: 100nF; C_0805_2012Metric_Pad1.18x1.45mm_HandSolder; not fitted
D1, D2, D3, D4: 1N4148; D_SOD-323_HandSoldering
M1, M2, M3, M4: Motor_DC; SolderWire-0.1sqmm_1x02_P3.6mm_D0.4mm_OD1mm
Q1, Q2, Q3, Q4: AO3400A; SOT-23_Handsoldering
R4, R5, R8, R9: 220; R_0805_2012Metric_Pad1.20x1.40mm_HandSolder
R6, R7, R10, R11: 10k; R_0805_2012Metric_Pad1.20x1.40mm_HandSolder

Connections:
+BATT: C18.1, C19.1, C20.1, C21.1, D1.1 (K), D2.1 (K), D3.1 (K), D4.1 (K), M1.1 (+), M2.1 (+), M3.1 (+), M4.1 (+); also elsewhere on the board
GND: Q1.2 (S), Q2.2 (S), Q3.2 (S), Q4.2 (S), R6.2, R7.2, R10.2, R11.2; also elsewhere on the board
MOTOR1: R4.1, R6.1; also elsewhere on the board
MOTOR2: R5.1, R7.1; also elsewhere on the board
MOTOR3: R8.1, R10.1; also elsewhere on the board
MOTOR4: R9.1, R11.1; also elsewhere on the board
unnamed: C19.2, D1.2 (A), M1.2 (-), Q1.3 (D)
unnamed: C18.2, D2.2 (A), M2.2 (-), Q2.3 (D)
unnamed: C20.2, D3.2 (A), M3.2 (-), Q3.3 (D)
unnamed: C21.2, D4.2 (A), M4.2 (-), Q4.3 (D)
unnamed: Q1.1 (G), R4.2
unnamed: Q2.1 (G), R5.2
unnamed: Q3.1 (G), R8.2
unnamed: Q4.1 (G), R9.2

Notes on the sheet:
Pulldown
Motor 2 (SW)
Flyback Diode
Motor 1 (SE)
Motor 3 (NE)
Motor 4 (NW)

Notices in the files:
README.md:
https://img.shields.io/badge/Code%20license-GPLv3-red?style=flat-square
